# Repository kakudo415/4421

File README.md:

# 4421

| Number | Meaning  |
| -----: | :------- |
|     44 | 44 Keys  |
|      2 | Separate |
|      1 | Number 1 |

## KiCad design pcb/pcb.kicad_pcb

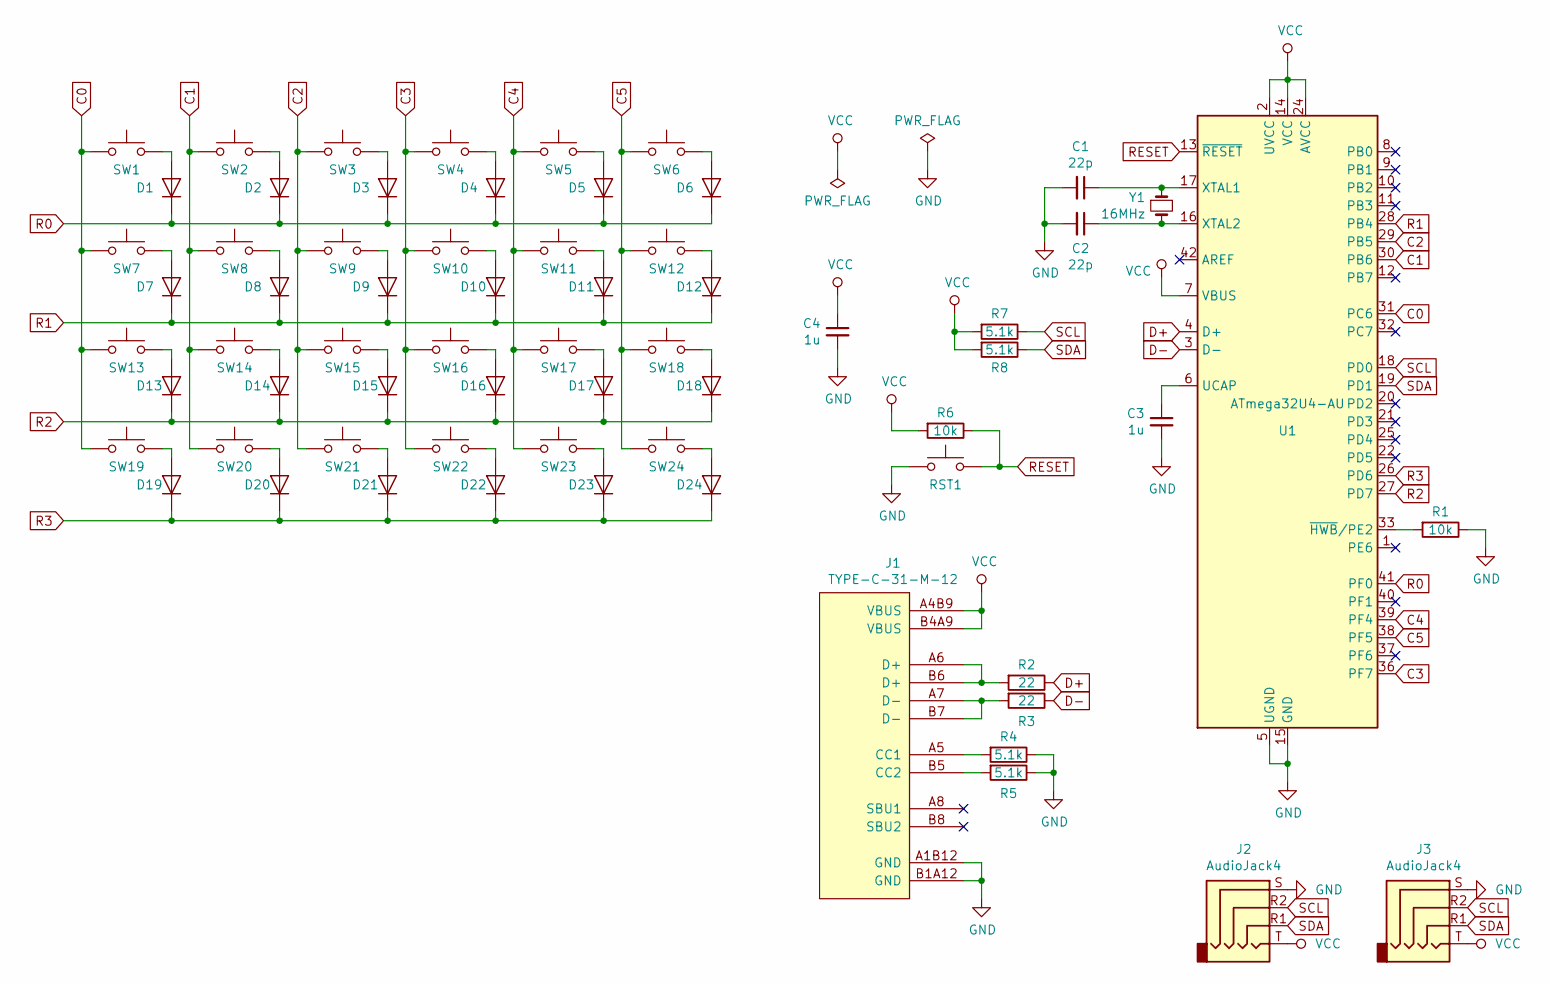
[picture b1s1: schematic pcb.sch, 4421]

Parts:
C1, C2: 22p; 2012M
C3, C4: 1u; 2012M
D1, D2, D3, D4, D5, D6, D7, D8, D9, D10, D11, D12, D13, D14, D15, D16, D17, D18, D19, D20, D21, D22, D23, D24: D; SOD123
J1: TYPE-C-31-M-12
J2, J3: AudioJack4; MJ-4PP-9
R1, R6: 10k; 2012M
R2, R3: 22; 2012M
R4, R5, R7, R8: 5.1k; 2012M
RST1: SW_Push; SW_SPST_TL3342
SW1, SW2, SW3, SW4, SW5, SW6, SW7, SW8, SW9, SW10, SW11, SW12, SW13, SW14, SW15, SW16, SW17, SW18, SW19, SW20, SW21, SW22, SW23, SW24: SW_Push; 1u
U1: ATmega32U4-AU; TQFP44
Y1: 16MHz; Crystal-HC-49-S

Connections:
C0: SW1.1, SW7.1, SW13.1, SW19.1, U1.31 (PC6)
C1: SW2.1, SW8.1, SW14.1, SW20.1, U1.30 (PB6)
C2: SW3.1, SW9.1, SW15.1, SW21.1, U1.29 (PB5)
C3: SW4.1, SW10.1, SW16.1, SW22.1, U1.36 (PF7)
C4: SW5.1, SW11.1, SW17.1, SW23.1, U1.39 (PF4)
C5: SW6.1, SW12.1, SW18.1, SW24.1, U1.38 (PF5)
D+: R2.1, U1.4 (D+)
D-: R3.1, U1.3 (D-)
GND: C1.2, C2.2, C3.2, C4.2, J1.A1B12 (GND), J1.B1A12 (GND), J2.S, J3.S, R1.1, R4.1, R5.1, RST1.1, U1.5 (UGND), U1.15 (GND), U1.23 (GND), U1.35 (GND), U1.43 (GND)
unnamed: C1.1, U1.17 (XTAL1), Y1.1
unnamed: C2.1, U1.16 (XTAL2), Y1.2
unnamed: C3.1, U1.6 (UCAP)
unnamed: D1.2 (A), SW1.2
unnamed: D2.2 (A), SW2.2
unnamed: D3.2 (A), SW3.2
unnamed: D4.2 (A), SW4.2
unnamed: D5.2 (A), SW5.2
unnamed: D6.2 (A), SW6.2
unnamed: D7.2 (A), SW7.2
unnamed: D8.2 (A), SW8.2
unnamed: D9.2 (A), SW9.2
unnamed: D10.2 (A), SW10.2
unnamed: D11.2 (A), SW11.2
unnamed: D12.2 (A), SW12.2
unnamed: D13.2 (A), SW13.2
unnamed: D14.2 (A), SW14.2
unnamed: D15.2 (A), SW15.2
unnamed: D16.2 (A), SW16.2
unnamed: D17.2 (A), SW17.2
unnamed: D18.2 (A), SW18.2
unnamed: D19.2 (A), SW19.2
unnamed: D20.2 (A), SW20.2
unnamed: D21.2 (A), SW21.2
unnamed: D22.2 (A), SW22.2
unnamed: D23.2 (A), SW23.2
unnamed: D24.2 (A), SW24.2
unnamed: J1.A5 (CC1), R4.2
unnamed: J1.A6 (D+), J1.B6 (D+), R2.2
unnamed: J1.A7 (D-), J1.B7 (D-), R3.2
unnamed: J1.B5 (CC2), R5.2
unnamed: R1.2, U1.33 (~HWB~/PE2)
R0: D1.1 (K), D2.1 (K), D3.1 (K), D4.1 (K), D5.1 (K), D6.1 (K), U1.41 (PF0)
R1: D7.1 (K), D8.1 (K), D9.1 (K), D10.1 (K), D11.1 (K), D12.1 (K), U1.28 (PB4)
R2: D13.1 (K), D14.1 (K), D15.1 (K), D16.1 (K), D17.1 (K), D18.1 (K), U1.27 (PD7)
R3: D19.1 (K), D20.1 (K), D21.1 (K), D22.1 (K), D23.1 (K), D24.1 (K), U1.26 (PD6)
RESET: R6.1, RST1.2, U1.13 (~RESET)
SCL: J2.R2, J3.R2, R7.1, U1.18 (PD0)
SDA: J2.R1, J3.R1, R8.1, U1.19 (PD1)
VCC: C4.1, J1.A4B9 (VBUS), J1.B4A9 (VBUS), J2.T, J3.T, R6.2, R7.2, R8.2, U1.2 (UVCC), U1.7 (VBUS), U1.14 (VCC), U1.24 (AVCC), U1.34 (VCC), U1.44 (AVCC)

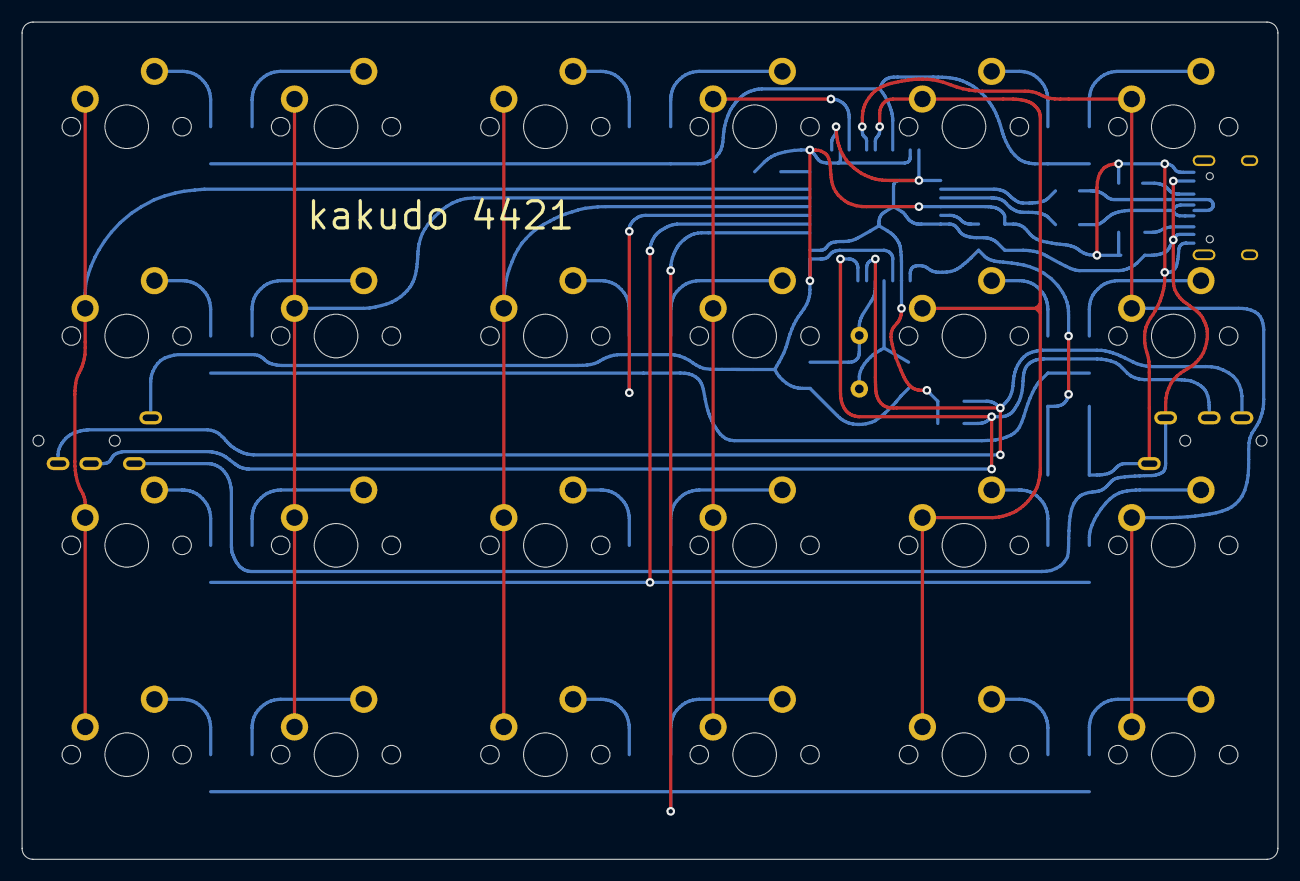
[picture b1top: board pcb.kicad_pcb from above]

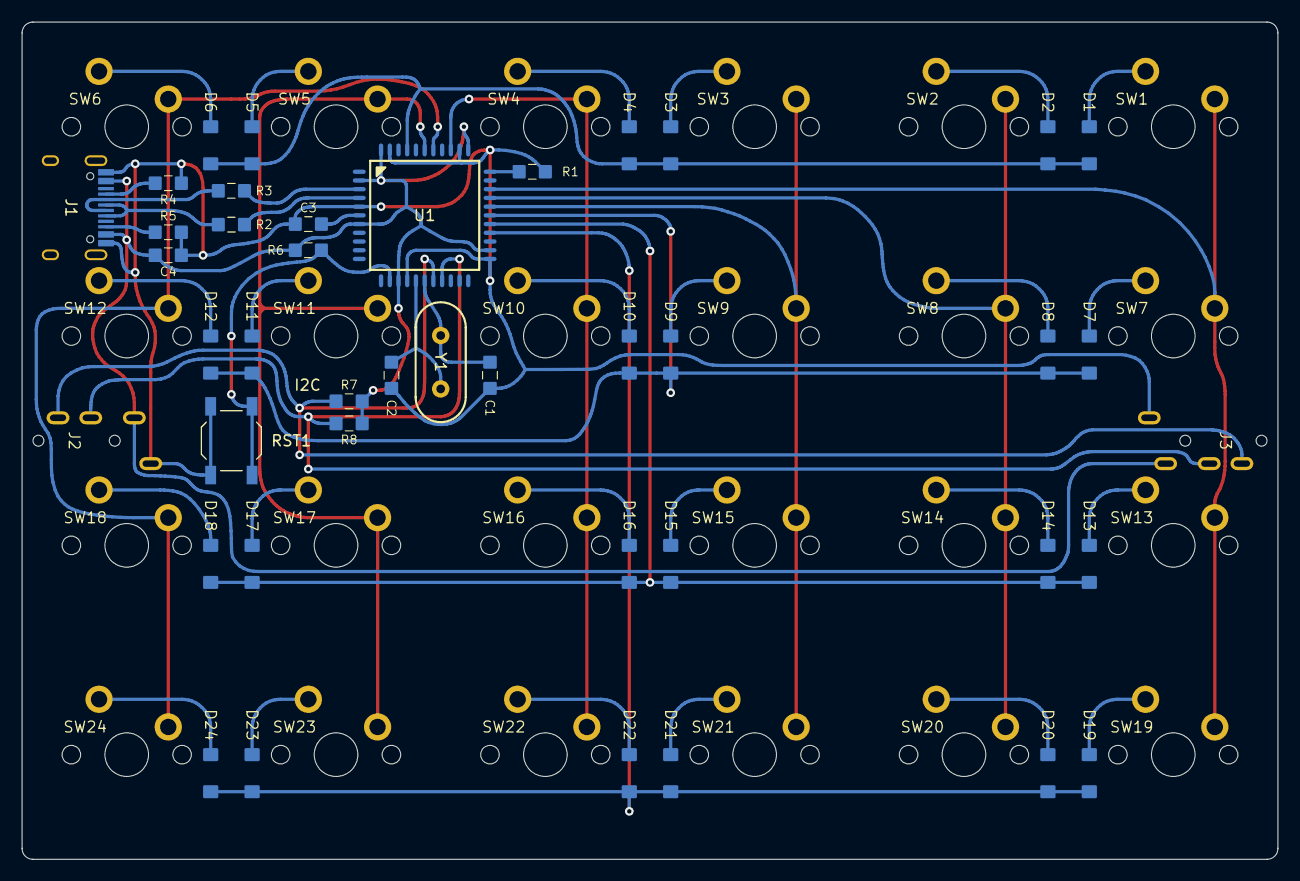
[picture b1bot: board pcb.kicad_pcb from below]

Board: 2 copper layers, 115.2 x 76.8 mm, 66 parts (41 on the bottom side), 49 nets.

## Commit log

2020-06-24 + description of product name
2020-06-24 pcb initialize
2020-06-26 + outline
2020-07-03 roundish(?)
2020-07-04 squarer design.
2020-07-05 bezier corner
2020-07-05 take out libraries w/ temporary continuous_corner
2020-07-05 +chamfered_square
2020-07-05 bezier corner -> continuous corner
2020-07-08 + continuous_corner (90degree only)
2020-07-08 clean continuous_corner()
2020-07-19 upper case
2020-07-20 refactoring
2020-07-20 upper & lower cases
2020-07-20 both sides
2020-07-23 + libraries
2020-07-23 height -> 24mm
2020-07-23 schematic outline
2020-08-10 adjust footprint library to 4421
2020-08-10 parts align (without trrs jack)
2020-08-11 + TRRS
2020-08-11 routing done
2020-08-11 routing with curve
2020-08-11 same length usb routing
2020-08-11 + side hole & + switch opener friendly key hole
2020-08-11 audio connector offset
2020-08-11 silk align
2020-08-11 both side usb connector
2020-08-11 symmetry
2020-08-11 through screw hole
2020-08-12 routing beautify & product number
2020-08-12 + gerber_to_order
2020-08-13 smd 2012 beautify
2020-08-13 + reset button
2020-08-13 plot for jlcpcb
2020-08-13 comment outed plate exporter
2020-08-14 key hole style rouded
2020-08-15 bigger plate holder & hexagon nuts
2020-08-15 coordinate simplified
2020-08-15 + schematic PDF
2020-08-19 USB-C receptacle hole circlize(?)
2020-08-21 screw hole adjust
2020-08-22 change shape of nut hole
2020-08-24 + I2C pullup
2020-08-24 silk change
2020-10-21 高さ修正
2020-10-21 キーの引っ掛かりを解消するための逃がし
